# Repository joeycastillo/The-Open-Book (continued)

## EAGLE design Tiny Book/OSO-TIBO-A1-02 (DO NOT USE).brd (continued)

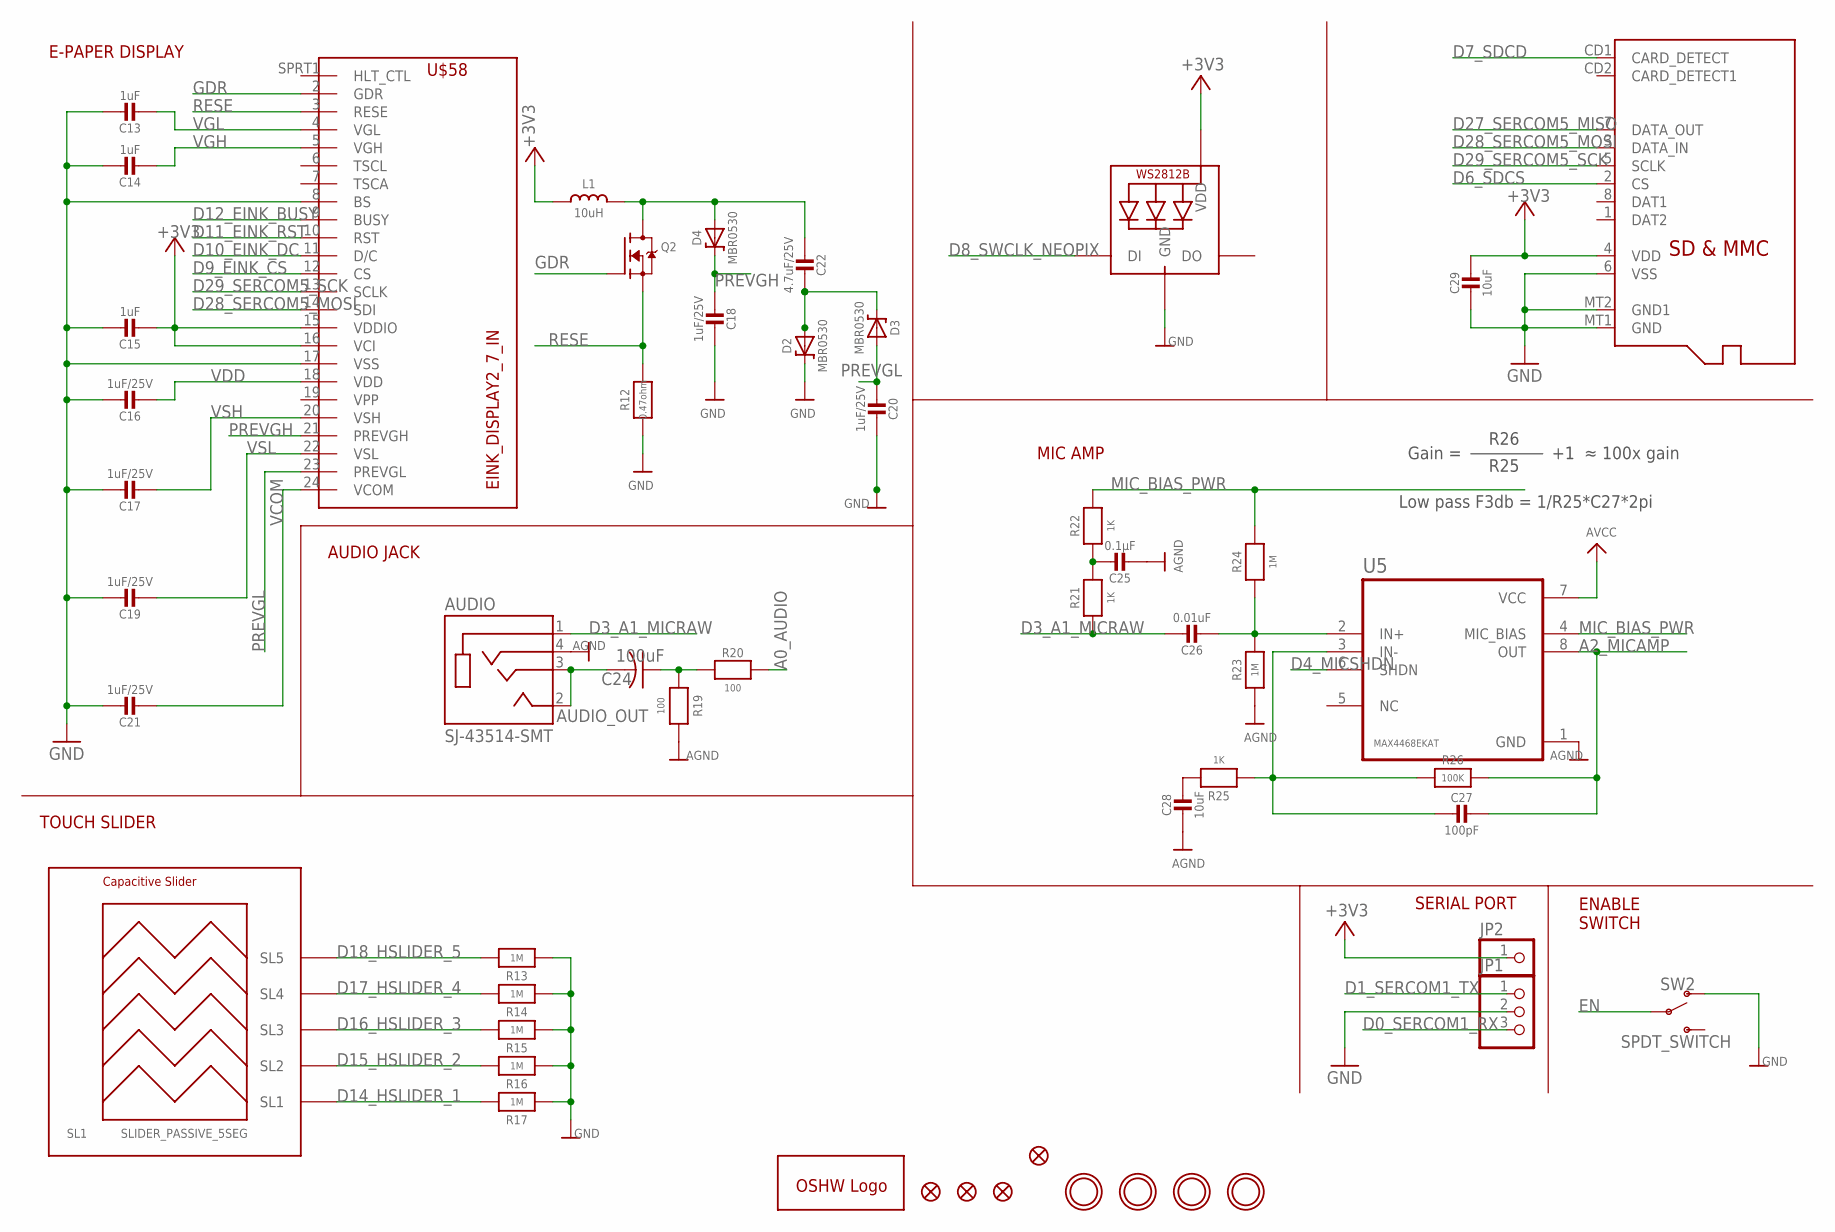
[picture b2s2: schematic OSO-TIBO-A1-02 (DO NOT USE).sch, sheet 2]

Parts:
AUDIO: SJ-43514-SMT; CUI_SJ-43514-SMT
C13, C14, C15: 1uF; 0805_10MGAP
C16, C17, C18, C19, C20, C21: 1uF/25V; 0805_10MGAP
C22: 4.7uF/25V; 0805-NO
C24: 100uF; C1210
C25: 0.1µF; 0805-NO
C26: 0.01uF; 0805-NO
C27: 100pF; 0805-NO
C28: 10uF; 0805-NO
C29: 10uF; 0805_10MGAP
D2, D3, D4: MBR0530; SOD-123
D8_NEOPIXEL: WS2812B_4020
FID1, FID2, FID3, FID4: FIDUCIAL_1MM
GOLD_ORB_SM1: OSHWLOGOLOGO5MM; OSHW_5MM
JP1: PINHD-1X3; 1X03
JP2: PINHD-1X1; 1X01
L1: 10uH; INDUCTOR_4X4MM_NR401
MICROSD: MICROSD
Q2: IRLML0100; SOT23-3
R12: 0.47ohm; 0805_10MGAP
R13, R14, R15, R16, R17, R23, R24: 1M; 0805-NO
R19, R20: 100; 0805-NO
R21, R22, R25: 1K; 0805-NO
R26: 100K; 0805-NO
SL1: SLIDER_PASSIVE_5SEG; SLIDER_PASSIVE_5SEG_12MM
SW2: SPDT_SWITCH; A10767
U5: MAX4468EKAT; SOT65P280X145-8N
U$1, U$4, U$5, U$7: MOUNTINGHOLE2.5; MOUNTINGHOLE_2.5_PLATED
U$58: EINK_DISPLAY2_7_IN; EINK_DISPLAY_2_7_IN

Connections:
+3V3: C15.2, C29.1, D8_NEOPIXEL.2 (VDD), JP2.1, L1.P$2 (2), MICROSD.4 (VDD), U$58.15 (VDDIO), U$58.16 (VCI); also elsewhere on the board
A0_AUDIO: R20.1; also elsewhere on the board
A2_MICAMP: C27.1, R26.2, U5.8 (OUT); also elsewhere on the board
AGND: AUDIO.4 (RING2), C25.2, C28.2, R19.1, R23.1, U5.1 (GND); also elsewhere on the board
AUDIO_OUT: AUDIO.2 (TIP), AUDIO.3 (RING1), C24.2
AVCC: U5.7 (VCC); also elsewhere on the board
D0_SERCOM1_RX: JP1.3; also elsewhere on the board
D1_SERCOM1_TX: JP1.1; also elsewhere on the board
D3_A1_MICRAW: AUDIO.1 (SLEEVE), C26.1, R21.1; also elsewhere on the board
D4_MICSHDN: U5.6 (SHDN); also elsewhere on the board
D6_SDCS: MICROSD.2 (CS); also elsewhere on the board
D7_SDCD: MICROSD.CD1 (CARD_DETECT); also elsewhere on the board
D8_SWCLK_NEOPIX: D8_NEOPIXEL.1 (DI); also elsewhere on the board
D9_EINK_CS: U$58.12 (CS); also elsewhere on the board
D10_EINK_DC: U$58.11 (D/C); also elsewhere on the board
D11_EINK_RST: U$58.10 (RST); also elsewhere on the board
D12_EINK_BUSY: U$58.9 (BUSY); also elsewhere on the board
D14_HSLIDER_1: R17.2, SL1.SL1; also elsewhere on the board
D15_HSLIDER_2: R16.2, SL1.SL2; also elsewhere on the board
D16_HSLIDER_3: R15.2, SL1.SL3; also elsewhere on the board
D17_HSLIDER_4: R14.2, SL1.SL4; also elsewhere on the board
D18_HSLIDER_5: R13.2, SL1.SL5; also elsewhere on the board
D27_SERCOM5_MISO: MICROSD.7 (DATA_OUT); also elsewhere on the board
D28_SERCOM5_MOSI: MICROSD.3 (DATA_IN), U$58.14 (SDI); also elsewhere on the board
D29_SERCOM5_SCK: MICROSD.5 (SCLK), U$58.13 (SCLK); also elsewhere on the board
EN: SW2.P$2; also elsewhere on the board
GDR: Q2.1 (G), U$58.2 (GDR)
GND: C13.1, C14.1, C15.1, C16.1, C17.1, C18.2, C19.1, C20.2, C21.1, C29.2, D2.C, D8_NEOPIXEL.4 (GND), JP1.2, MICROSD.6 (VSS), MICROSD.MT1 (GND), MICROSD.MT2 (GND1), R12.2, R13.1, R14.1, R15.1, R16.1, R17.1, SW2.P$1 (O), U$58.8 (BS), U$58.17 (VSS); also elsewhere on the board
MIC_BIAS_PWR: R22.2, R24.2, U5.4 (MIC_BIAS)
unnamed: C22.2, D2.A, D3.C
unnamed: C22.1, D4.A, L1.P$1 (1), Q2.3 (D)
unnamed: C24.1, R19.2, R20.2
unnamed: C25.1, R21.2, R22.1
unnamed: C26.2, R23.2, R24.1, U5.2 (IN+)
unnamed: C27.2, R25.1, R26.1, U5.3 (IN-)
unnamed: C28.1, R25.2
PREVGH: C18.1, D4.C, U$58.21 (PREVGH)
PREVGL: C20.1, D3.A, U$58.23 (PREVGL)
RESE: Q2.2 (S), R12.1, U$58.3 (RESE)
VCOM: C21.2, U$58.24 (VCOM)
VDD: C16.2, U$58.18 (VDD)
VGH: C14.2, U$58.5 (VGH)
VGL: C13.2, U$58.4 (VGL)
VSH: C17.2, U$58.20 (VSH)
VSL: C19.2, U$58.22 (VSL)

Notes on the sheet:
E-PAPER DISPLAY
ENABLE SWITCH
SERIAL PORT
Gain =
R26
R25
≈ 100x gain
Low pass F3db = 1/R25*C27*2pi
MIC AMP
AUDIO JACK
TOUCH SLIDER

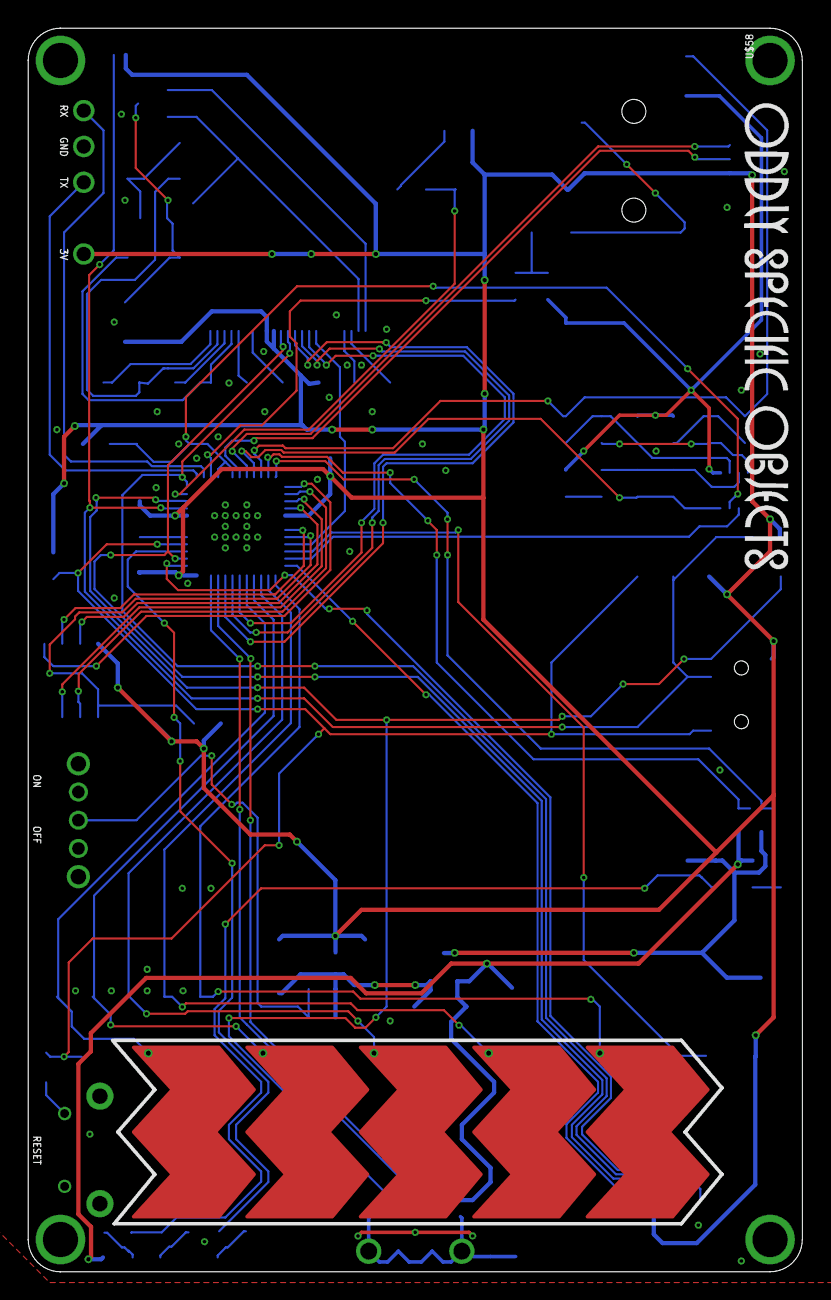
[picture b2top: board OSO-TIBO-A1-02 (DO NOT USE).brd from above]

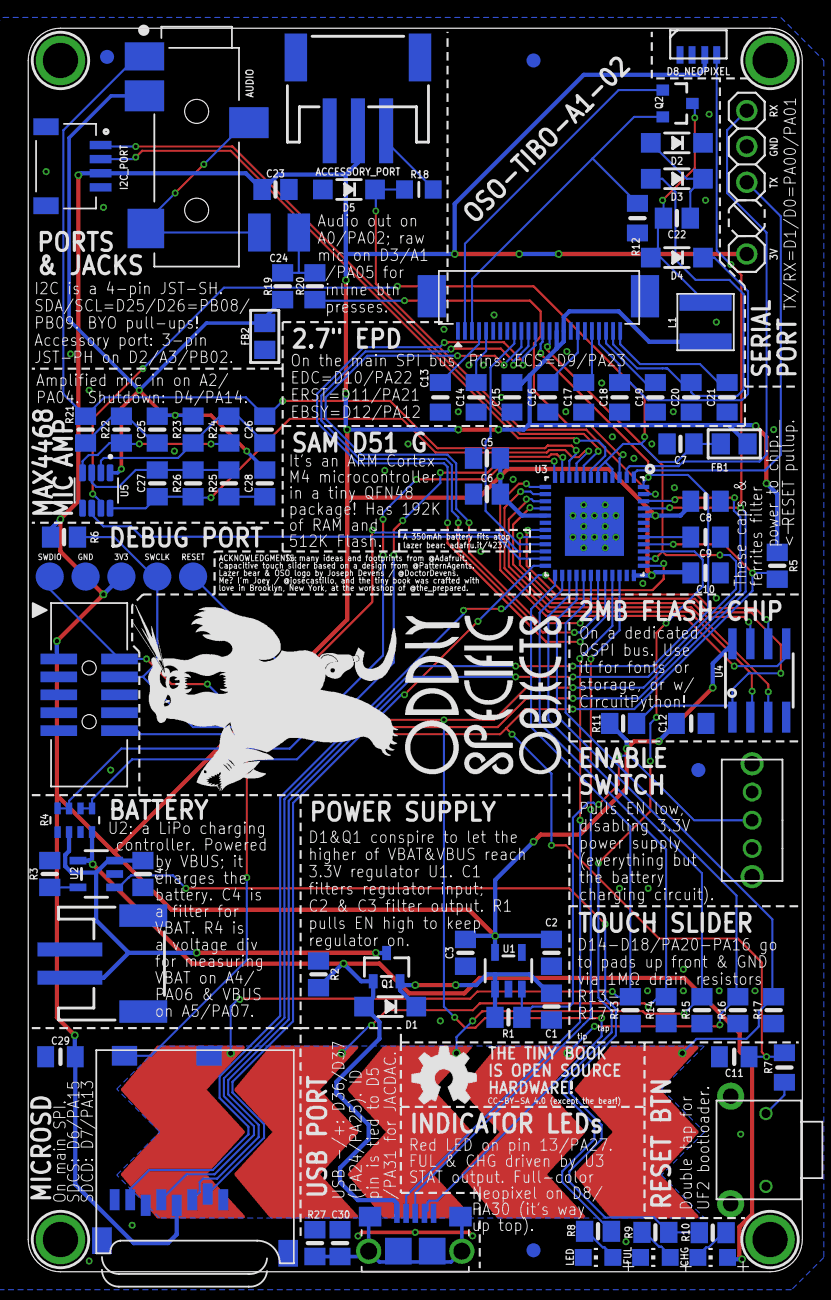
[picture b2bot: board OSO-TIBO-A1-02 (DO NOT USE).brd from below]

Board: 2 copper layers, 54.9 x 88.1 mm, 106 parts (103 on the bottom side), 73 nets.

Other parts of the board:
U$37: OSO_WORDMARK_THREELINE_450MIL_1000DPI
U$41: OSO_BEAR_525X750MIL_1000DPI
U$42: OSO_WORDMARK_125X1300MIL_1000DPI

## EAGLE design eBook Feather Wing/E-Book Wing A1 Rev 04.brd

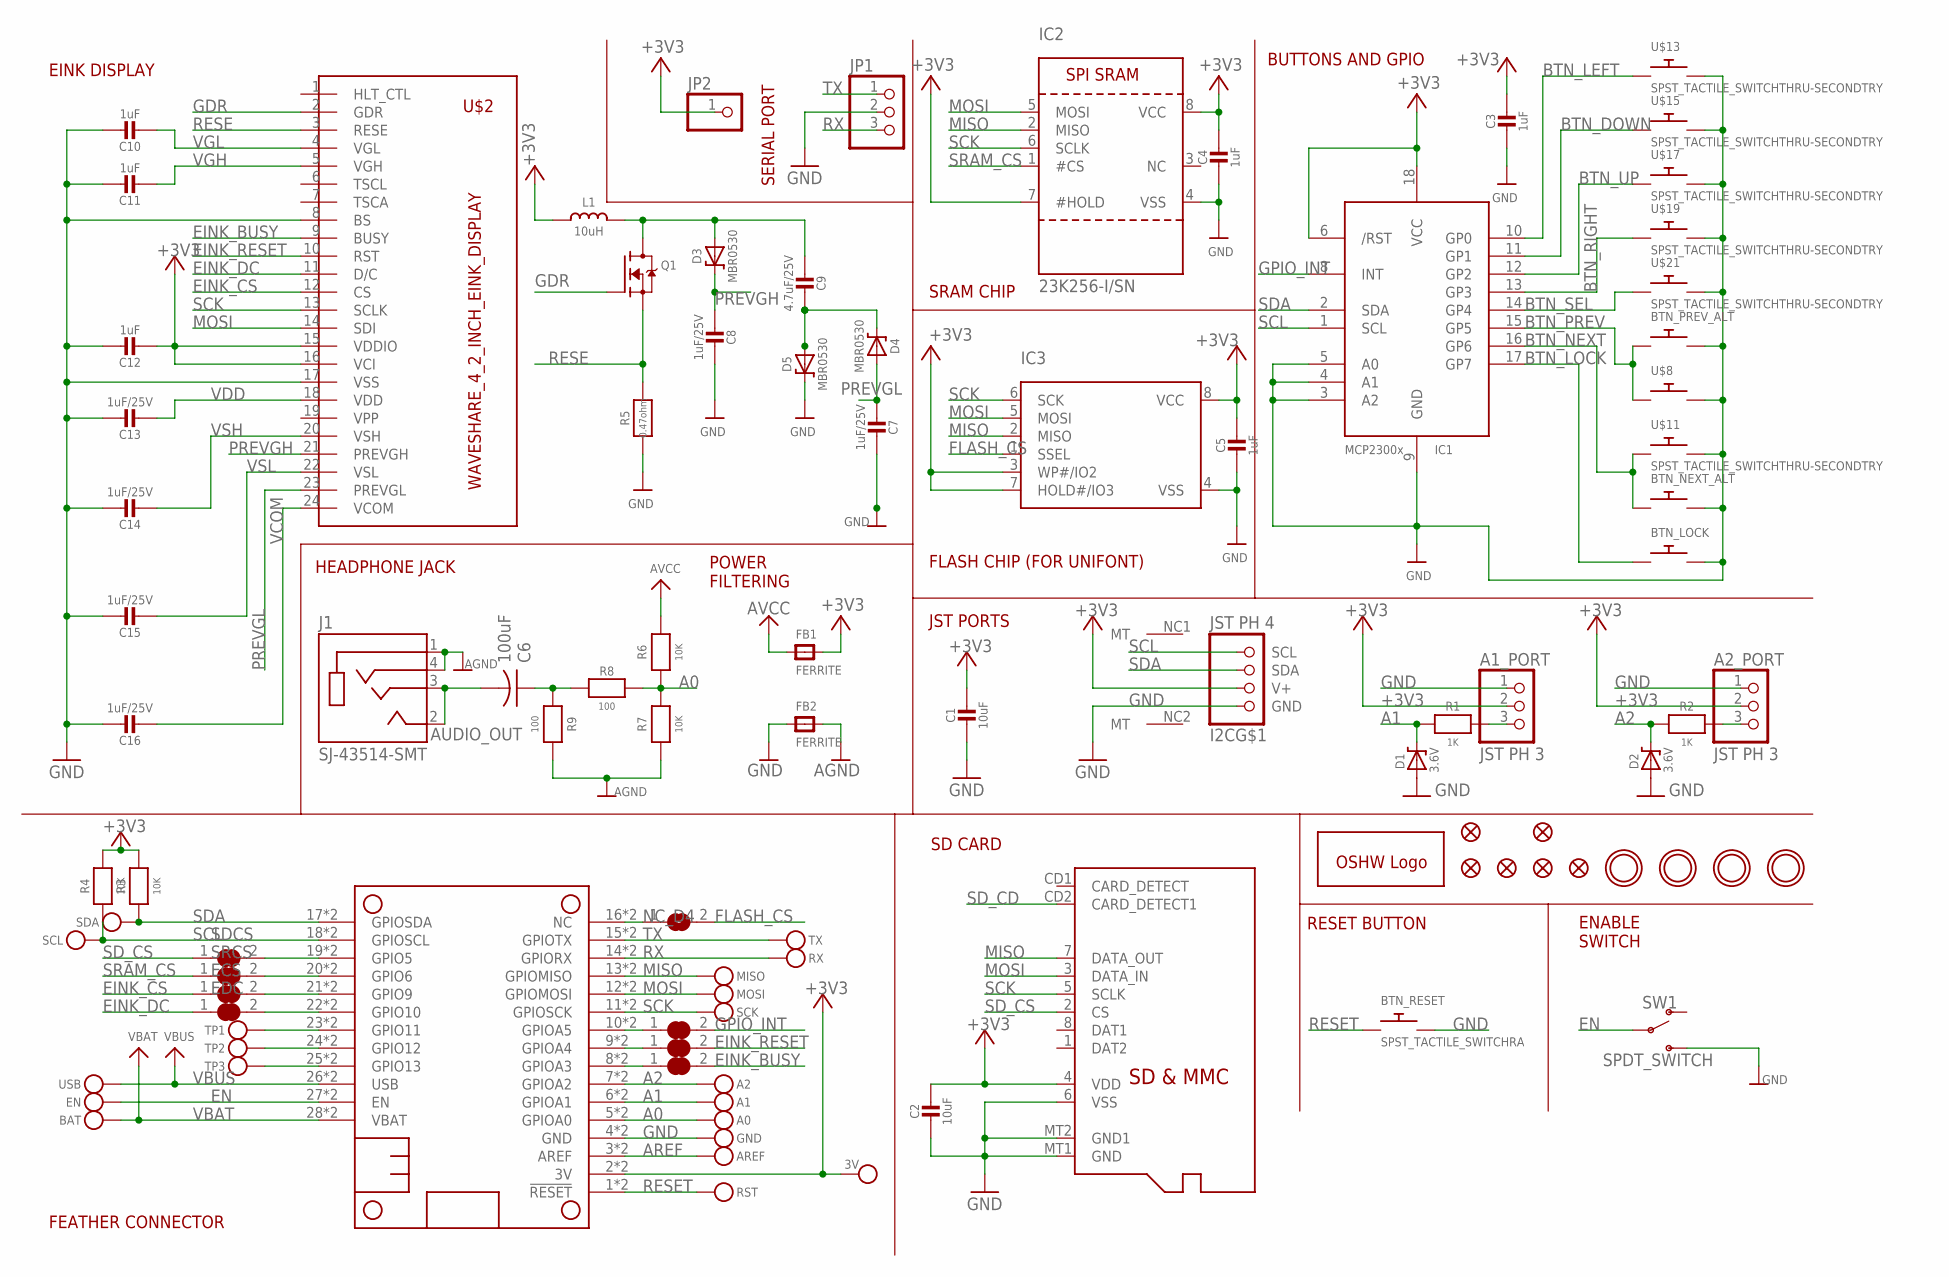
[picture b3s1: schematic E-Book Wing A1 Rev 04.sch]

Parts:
3V: MICROBUILDER_TESTPOINT1.5X2.0MM_NOCREAM; MICROBUILDER_PAD-1.5X2.0
A0, A1, A2: MICROBUILDER_TESTPOINT1.5X2.0MM_NOCREAM; MICROBUILDER_PAD-1.5X2.0
A1_PORT, A2_PORT: JST PH 3; JSTPH3
AREF: MICROBUILDER_TESTPOINT1.5X2.0MM_NOCREAM; MICROBUILDER_PAD-1.5X2.0
BAT: MICROBUILDER_TESTPOINT1.5X2.0MM_NOCREAM; MICROBUILDER_PAD-1.5X2.0
BTN_LOCK: SPST_TACTILE_SWITCHRA; TL3330AF130QG
BTN_NEXT_ALT: SPST_TACTILE_SWITCHRA; TL3330AF130QG
BTN_PREV_ALT: SPST_TACTILE_SWITCHRA; TL3330AF130QG
BTN_RESET: SPST_TACTILE_SWITCHRA; TL3330AF130QG
C1: 10uF; 0805-NO
C2: 10uF; 0805_10MGAP
C3, C4, C5: 1uF; 0805_10MGAP
C6: 100uF; C1210
C7, C8, C13, C14, C15, C16: 1uF/25V; 0805-NO
C9: 4.7uF/25V; 0805-NO
C10, C11, C12: 1uF; 0805-NO
D1, D2: 3.6V; SOD-123
D3, D4, D5: MBR0530; SOD-123
EBSY: MICROBUILDER_SOLDERJUMPER_CLOSED; MICROBUILDER_SOLDERJUMPER_CLOSEDWIRE
ECS: MICROBUILDER_SOLDERJUMPER_CLOSED; MICROBUILDER_SOLDERJUMPER_CLOSEDWIRE
EDC: MICROBUILDER_SOLDERJUMPER_CLOSED; MICROBUILDER_SOLDERJUMPER_CLOSEDWIRE
EN: MICROBUILDER_TESTPOINT1.5X2.0MM_NOCREAM; MICROBUILDER_PAD-1.5X2.0
ERST: MICROBUILDER_SOLDERJUMPER_CLOSED; MICROBUILDER_SOLDERJUMPER_CLOSEDWIRE
FB1, FB2: FERRITE; 0805
FCS: SOLDERJUMPER_OPEN
FID1, FID2, FID3, FID4, FID5, FID6: FIDUCIAL_1MM
GND: MICROBUILDER_TESTPOINT1.5X2.0MM_NOCREAM; MICROBUILDER_PAD-1.5X2.0
GOLD_ORB_SM1: OSHWLOGOLOGO5MM; OSHW_5MM
I2C: JST PH 4; JSTPH4
IC1: MCP23008/SO; SO18W
IC2: 23K256-I/SN; SOIC8_150MIL
IC3: MICROBUILDER_SPIFLASH_SOIC8; MICROBUILDER_SOIC8_150MIL
INT: MICROBUILDER_SOLDERJUMPER_CLOSED; MICROBUILDER_SOLDERJUMPER_CLOSEDWIRE
J1: SJ-43514-SMT; CUI_SJ-43514-SMT
JP1: PINHD-1X3; 1X03
JP2: PINHD-1X1; 1X01
L1: 10uH; INDUCTOR_4X4MM_NR401
MICROSD: MICROSD
MISO: MICROBUILDER_TESTPOINT1.5X2.0MM_NOCREAM; MICROBUILDER_PAD-1.5X2.0
MOSI: MICROBUILDER_TESTPOINT1.5X2.0MM_NOCREAM; MICROBUILDER_PAD-1.5X2.0
MS1: MICROBUILDER_FEATHERWING_SMTDUAL; MICROBUILDER_FEATHERWING_SMT2
Q1: IRLML0100; SOT23-3
R1, R2: 1K; _0805MP
R3, R4, R6, R7: 10K; _0805MP
R5: 0.47ohm; 0805_10MGAP
R8, R9: 100; _0805MP
RST: MICROBUILDER_TESTPOINT1.5X2.0MM_NOCREAM; MICROBUILDER_PAD-1.5X2.0
RX: MICROBUILDER_TESTPOINT1.5X2.0MM_NOCREAM; MICROBUILDER_PAD-1.5X2.0
SCK: MICROBUILDER_TESTPOINT1.5X2.0MM_NOCREAM; MICROBUILDER_PAD-1.5X2.0
SCL: MICROBUILDER_TESTPOINT1.5X2.0MM_NOCREAM; MICROBUILDER_PAD-1.5X2.0
SDA: MICROBUILDER_TESTPOINT1.5X2.0MM_NOCREAM; MICROBUILDER_PAD-1.5X2.0
SDCS: MICROBUILDER_SOLDERJUMPER_CLOSED; MICROBUILDER_SOLDERJUMPER_CLOSEDWIRE
SRCS: MICROBUILDER_SOLDERJUMPER_CLOSED; MICROBUILDER_SOLDERJUMPER_CLOSEDWIRE
SW1: SPDT_SWITCH; A10767
TP1, TP2, TP3: MICROBUILDER_TESTPOINT1.5X2.0MM_NOCREAM; MICROBUILDER_PAD-1.5X2.0
TX: MICROBUILDER_TESTPOINT1.5X2.0MM_NOCREAM; MICROBUILDER_PAD-1.5X2.0
U$1, U$4, U$5, U$7: MOUNTINGHOLE2.5; MOUNTINGHOLE_2.5_PLATED
U$2: WAVESHARE_4_2_INCH_EINK_DISPLAY; EINK_DISPLAY_4_2IN
U$8, U$11, U$13, U$15, U$17, U$19, U$21: SPST_TACTILE_SWITCHTHRU-SECONDTRY; MJTP1250-TRY2
USB: MICROBUILDER_TESTPOINT1.5X2.0MM_NOCREAM; MICROBUILDER_PAD-1.5X2.0

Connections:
+3V3: 3V.P$1, A1_PORT.2, A2_PORT.2, C1.1, C2.1, C3.1, C4.1, C5.1, C12.2, FB1.2, I2C.2 (V+), IC1.6 (/RST), IC1.18 (VCC), IC2.7 (#HOLD), IC2.8 (VCC), IC3.3 (WP#/IO2), IC3.7 (HOLD#/IO3), IC3.8 (VCC), JP2.1, L1.P$2 (2), MICROSD.4 (VDD), MS1.2 (3V), MS1.2' (3V), R3.1, R4.1, U$2.15 (VDDIO), U$2.16 (VCI)
A0: A0.P$1, MS1.5 (GPIOA0), MS1.5' (GPIOA0), R6.2, R7.1, R8.1
A1: A1.P$1, D1.C, MS1.6 (GPIOA1), MS1.6' (GPIOA1), R1.2
A1_: A1_PORT.3, R1.1
A2: A2.P$1, D2.C, MS1.7 (GPIOA2), MS1.7' (GPIOA2), R2.2
A2_: A2_PORT.3, R2.1
AGND: FB2.2, J1.1 (SLEEVE), J1.4 (RING2), R7.2, R9.1
AREF: AREF.P$1, MS1.3 (AREF), MS1.3' (AREF)
AUDIO_OUT: C6.2, J1.2 (TIP), J1.3 (RING1)
AVCC: FB1.1, R6.1
BTN_DOWN: IC1.11 (GP1), U$15.P$1
BTN_LEFT: IC1.10 (GP0), U$13.P$1
BTN_LOCK: BTN_LOCK.P$1, IC1.17 (GP7)
BTN_NEXT: BTN_NEXT_ALT.P$1, IC1.16 (GP6), U$11.P$1
BTN_PREV: BTN_PREV_ALT.P$1, IC1.15 (GP5), U$8.P$1
BTN_RIGHT: IC1.13 (GP3), U$19.P$1
BTN_SEL: IC1.14 (GP4), U$21.P$1
BTN_UP: IC1.12 (GP2), U$17.P$1
EINK_BUSY: EBSY.2, U$2.9 (BUSY)
EINK_CS: ECS.1, U$2.12 (CS)
EINK_DC: EDC.1, U$2.11 (D/C)
EINK_RESET: ERST.2, U$2.10 (RST)
EN: EN.P$1, MS1.27 (EN), MS1.27' (EN), SW1.P$2
FLASH_CS: FCS.2, IC3.1 (SSEL)
GDR: Q1.1 (G), U$2.2 (GDR)
GND: A1_PORT.1, A2_PORT.1, BTN_LOCK.P$2, BTN_NEXT_ALT.P$2, BTN_PREV_ALT.P$2, BTN_RESET.P$2, C1.2, C2.2, C3.2, C4.2, C5.2, C7.2, C8.2, C10.1, C11.1, C12.1, C13.1, C14.1, C15.1, C16.1, D1.A, D2.A, D5.C, FB2.1, GND.P$1, I2C.1 (GND), IC1.3 (A2), IC1.4 (A1), IC1.5 (A0), IC1.9 (GND), IC2.4 (VSS), IC3.4 (VSS), JP1.2, MICROSD.6 (VSS), MICROSD.MT1 (GND), MICROSD.MT2 (GND1), MS1.4 (GND), MS1.4' (GND), R5.2, SW1.P$3 (S), U$2.8 (BS), U$2.17 (VSS), U$8.P$2, U$11.P$2, U$13.P$2, U$15.P$2, U$17.P$2, U$19.P$2, U$21.P$2
GPIO_INT: IC1.8 (INT), INT.2
MISO: IC2.2 (MISO), IC3.2 (MISO), MICROSD.7 (DATA_OUT), MISO.P$1, MS1.13 (GPIOMISO), MS1.13' (GPIOMISO)
MOSI: IC2.5 (MOSI), IC3.5 (MOSI), MICROSD.3 (DATA_IN), MOSI.P$1, MS1.12 (GPIOMOSI), MS1.12' (GPIOMOSI), U$2.14 (SDI)
unnamed: C6.1, R8.2, R9.2
unnamed: C9.2, D4.C, D5.A
unnamed: C9.1, D3.A, L1.P$1 (1), Q1.3 (D)
unnamed: MS1.25 (GPIO13), MS1.25' (GPIO13), TP3.P$1
unnamed: MS1.24 (GPIO12), MS1.24' (GPIO12), TP2.P$1
unnamed: MS1.23 (GPIO11), MS1.23' (GPIO11), TP1.P$1
NC_D4: FCS.1, MS1.16 (NC), MS1.16' (NC)
PREVGH: C8.1, D3.C, U$2.21 (PREVGH)
PREVGL: C7.1, D4.A, U$2.23 (PREVGL)
RESE: Q1.2 (S), R5.1, U$2.3 (RESE)
RESET: BTN_RESET.P$1, MS1.1 (!RESET), MS1.1' (!RESET), RST.P$1
RX: JP1.3, MS1.14 (GPIORX), MS1.14' (GPIORX), RX.P$1
SCK: IC2.6 (SCLK), IC3.6 (SCK), MICROSD.5 (SCLK), MS1.11 (GPIOSCK), MS1.11' (GPIOSCK), SCK.P$1, U$2.13 (SCLK)
SCL: I2C.4 (SCL), IC1.1 (SCL), MS1.18 (GPIOSCL), MS1.18' (GPIOSCL), R4.2, SCL.P$1
SDA: I2C.3 (SDA), IC1.2 (SDA), MS1.17 (GPIOSDA), MS1.17' (GPIOSDA), R3.2, SDA.P$1
SD_CD: MICROSD.CD2 (CARD_DETECT1)
SD_CS: MICROSD.2 (CS), SDCS.1
SRAM_CS: IC2.1 (#CS), SRCS.1
TX: JP1.1, MS1.15 (GPIOTX), MS1.15' (GPIOTX), TX.P$1
VBAT: BAT.P$1, MS1.28 (VBAT), MS1.28' (VBAT)
VBUS: MS1.26 (USB), MS1.26' (USB), USB.P$1
VCOM: C16.2, U$2.24 (VCOM)
VDD: C13.2, U$2.18 (VDD)
VGH: C11.2, U$2.5 (VGH)
VGL: C10.2, U$2.4 (VGL)
VSH: C14.2, U$2.20 (VSH)
VSL: C15.2, U$2.22 (VSL)
_EINK_BUSY: EBSY.1, MS1.8 (GPIOA3), MS1.8' (GPIOA3)
_EINK_CS: ECS.2, MS1.21 (GPIO9), MS1.21' (GPIO9)
_EINK_DC: EDC.2, MS1.22 (GPIO10), MS1.22' (GPIO10)
_EINK_RESET: ERST.1, MS1.9 (GPIOA4), MS1.9' (GPIOA4)
_GPIO_INT: INT.1, MS1.10 (GPIOA5), MS1.10' (GPIOA5)
_SD_CS: MS1.19 (GPIO5), MS1.19' (GPIO5), SDCS.2
_SRAM_CS: MS1.20 (GPIO6), MS1.20' (GPIO6), SRCS.2

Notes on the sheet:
FEATHER CONNECTOR
SD CARD
EINK DISPLAY
HEADPHONE JACK
RESET BUTTON
ENABLE SWITCH
POWER FILTERING
BUTTONS AND GPIO
JST PORTS
SRAM CHIP
FLASH CHIP (FOR UNIFONT)
SERIAL PORT

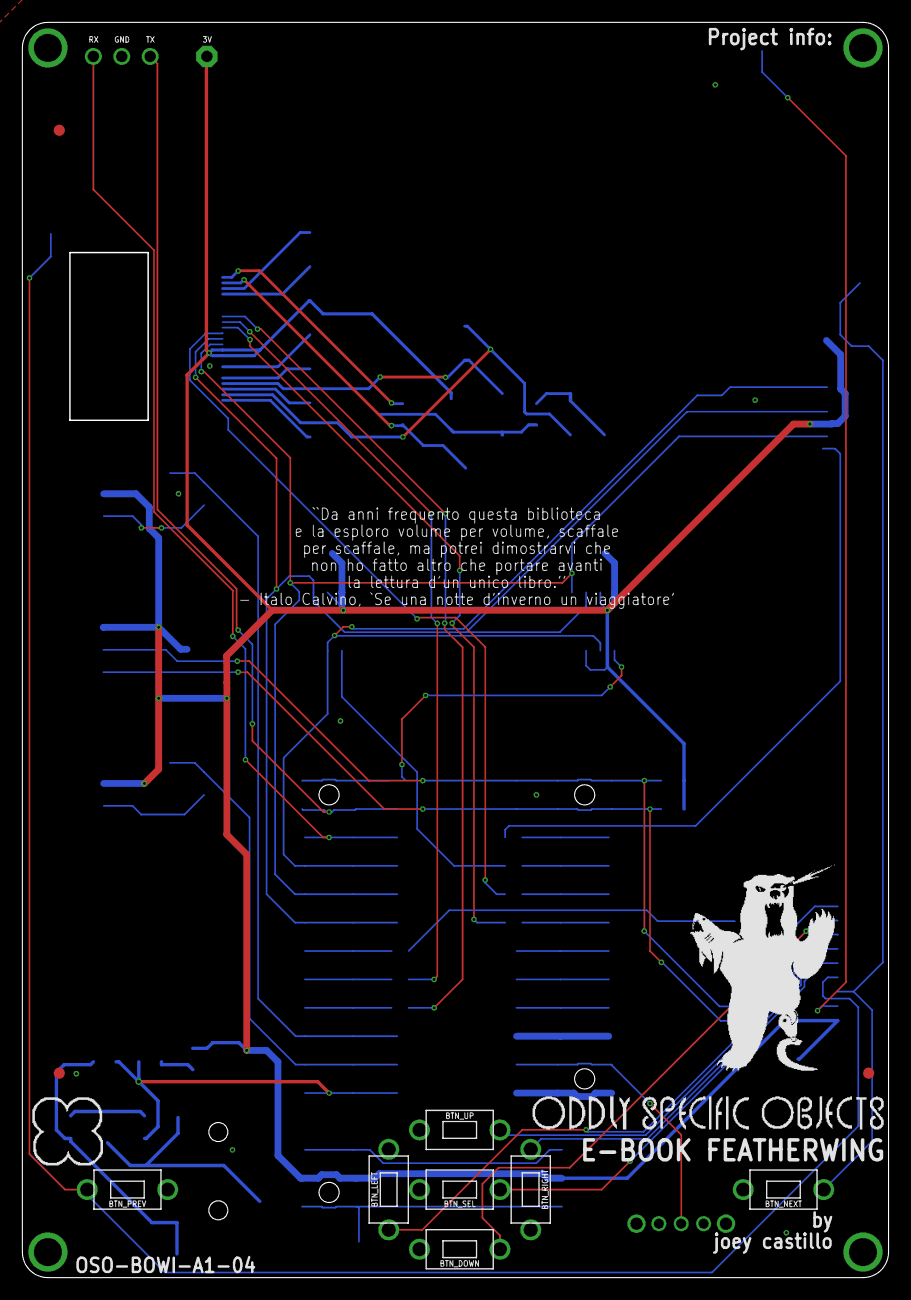
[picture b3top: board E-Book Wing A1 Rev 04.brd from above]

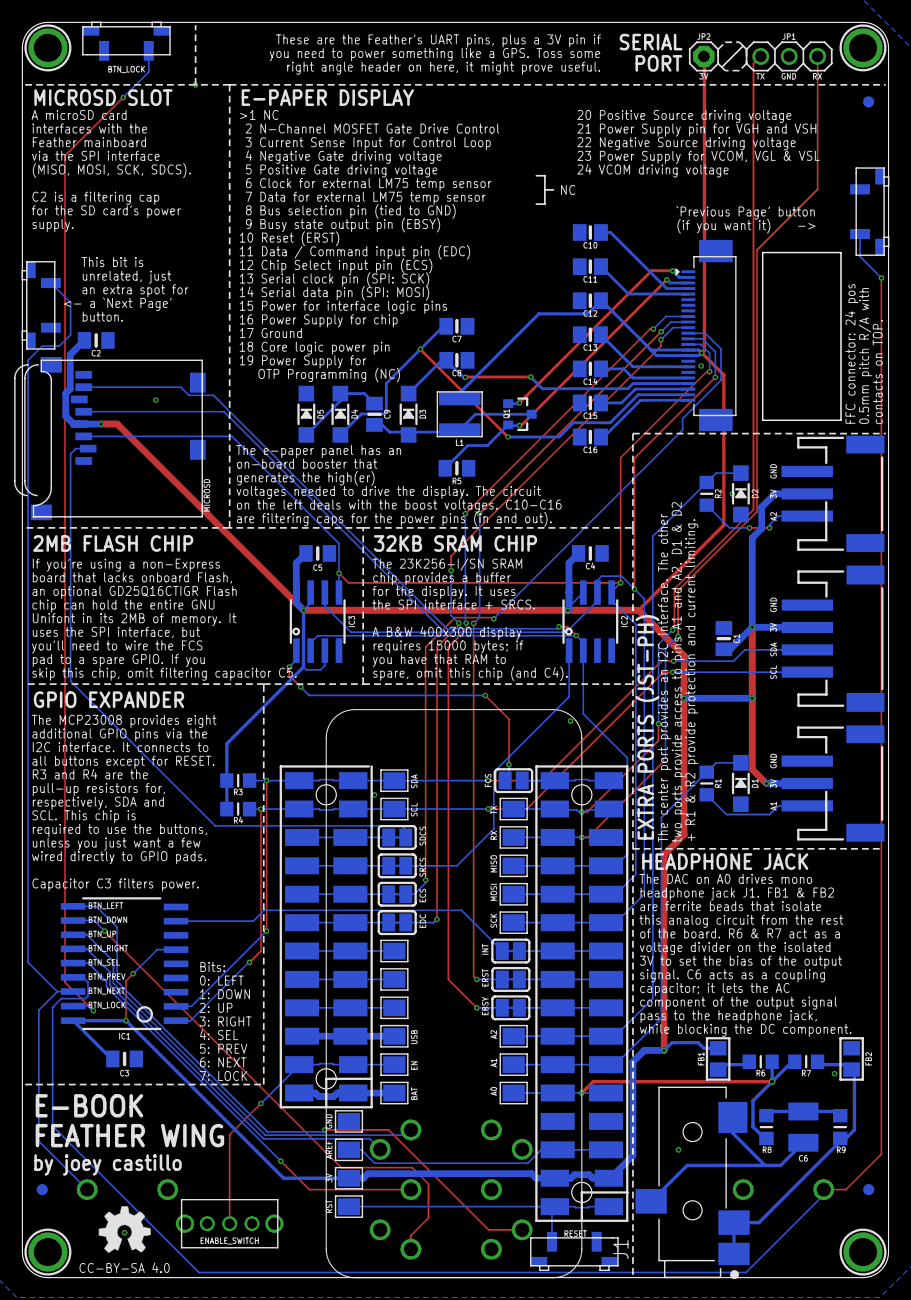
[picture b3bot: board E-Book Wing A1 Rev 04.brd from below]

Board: 2 copper layers, 77.5 x 112.3 mm, 100 parts (86 on the bottom side), 62 nets.

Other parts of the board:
U$44: OSO_GRAPHIC
U$45: OSO_BEAR; OSO_BEAR_750MIL
U$48: OSO_TEXTOSO_TEXT_ONELINE_125MIL; OSO_ONELINE_125MIL

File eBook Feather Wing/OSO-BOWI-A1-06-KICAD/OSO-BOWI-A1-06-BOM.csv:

Reference, Quantity, Value, Footprint, Datasheet
A1_PORT1 A2_PORT1 ,2,"JST PH 3","OSO-BOWI-A1-06:JSTPH3",""
BCS1 ,1,"SOLDERJUMPER_OPEN","OSO-BOWI-A1-06:SOLDERJUMPER_OPEN",""
BTN-RIGHT1 BTN_DOWN1 BTN_LEFT1 BTN_NEXT1 BTN_PREV1 BTN_SEL1 BTN_UP1 ,7,"SWITCH_PUSHBUTTONEVQ-PE","OSO-BOWI-A1-06:TACT_PANA-EVQ",""
BTN_LOCK1 BTN_RESET1 ,2,"SWITCH_PUSHBUTTONC&K_KSS","OSO-BOWI-A1-06:BTN_CK_KSS",""
C1 ,1,"10uF","OSO-BOWI-A1-06:0805-NO",""
C10 C11 C12 ,3,"1uF","OSO-BOWI-A1-06:0805-NO",""
C13 C14 C15 C16 C7 C8 ,6,"1uF/25V","OSO-BOWI-A1-06:0805-NO",""
C2 ,1,"10uF","OSO-BOWI-A1-06:0805_10MGAP",""
C3 C4 C5 ,3,"1uF","OSO-BOWI-A1-06:0805_10MGAP",""
C6 ,1,"100uF","OSO-BOWI-A1-06:C1210",""
C9 ,1,"4.7uF/25V","OSO-BOWI-A1-06:0805-NO",""
D1 D2 ,2,"3.6V","OSO-BOWI-A1-06:SOD-123",""
D3 D4 D5 ,3,"MBR0530","OSO-BOWI-A1-06:SOD-123",""
DNP_NEXT_ALT1 DNP_PREV_ALT1 ,2,"SPST_TACTILE_SWITCHRA","OSO-BOWI-A1-06:TL3330AF130QG",""
FB1 FB2 ,2,"FERRITE","OSO-BOWI-A1-06:0805",""
FID1 FID2 FID3 FID4 FID5 FID6 ,6,"FIDUCIAL_1MM","OSO-BOWI-A1-06:FIDUCIAL_1MM",""
GOLD_ORB_SM1 ,1,"OSHWLOGOLOGO5MM","OSO-BOWI-A1-06:OSHW_5MM",""
I2C1 ,1,"JST PH 4","OSO-BOWI-A1-06:JSTPH4",""
IC1 ,1,"MCP23008_SO","OSO-BOWI-A1-06:SO18W",""
IC2 ,1,"23K256-I/SN","OSO-BOWI-A1-06:SOIC8_150MIL",""
IC3 ,1,"MICROBUILDER_SPIFLASH_SOIC8","OSO-BOWI-A1-06:MICROBUILDER_SOIC8_150MIL",""
J1 ,1,"SJ-43514-SMT","OSO-BOWI-A1-06:CUI_SJ-43514-SMT",""
JP1 ,1,"PINHD-1X3","OSO-BOWI-A1-06:1X03",""
JP2 ,1,"PINHD-1X1","OSO-BOWI-A1-06:1X01",""
L1 ,1,"10uH","OSO-BOWI-A1-06:MICROBUILDER_INDUCTOR_4X4MM_NR401_BIGPADS",""
MICROSD1 ,1,"MICROSD","OSO-BOWI-A1-06:MICROSD",""
MS1 ,1,"MICROBUILDER_FEATHERWING_SMTDUAL_NOLINES","OSO-BOWI-A1-06:MICROBUILDER_FEATHERWING_SMT2_NOLINES",""
Q1 ,1,"IRLML0100","OSO-BOWI-A1-06:SOT23-3",""
R1 R2 ,2,"1K","OSO-BOWI-A1-06:_0805MP",""
R5 ,1,"0.47ohm","OSO-BOWI-A1-06:0805_10MGAP",""
R10 R11 R12 R13 R3 R4 R6 R7 ,8,"10K","OSO-BOWI-A1-06:_0805MP",""
R8 R9 ,2,"100","OSO-BOWI-A1-06:_0805MP",""
EBSY1 ECS1 EDC1 ERST1 INT1 SDCS1 SRCS1 ,7,"MICROBUILDER_SOLDERJUMPER_CLOSED","OSO-BOWI-A1-06:MICROBUILDER_SOLDERJUMPER_CLOSEDWIRE",""
SW1 ,1,"SPDT_SWITCH","OSO-BOWI-A1-06:A10767",""
3V3 A0 A1 A2 AREF1 BAT1 EN1 GND1 MISO1 MOSI1 RST1 RX1 SCK1 SCL1 SDA1 TP1 TP2 TP3 TX1 USB1 ,20,"MICROBUILDER_TESTPOINT1.5X2.0MM_NOCREAM","OSO-BOWI-A1-06:MICROBUILDER_PAD-1.5X2.0",""
U$1 U$4 U$5 U$7 ,4,"MOUNTINGHOLE2.5","OSO-BOWI-A1-06:MOUNTINGHOLE_2.5_PLATED",""
U$2 ,1,"WAVESHARE_4_2_INCH_EINK_DISPLAY","OSO-BOWI-A1-06:EINK_DISPLAY_4_2IN",""
